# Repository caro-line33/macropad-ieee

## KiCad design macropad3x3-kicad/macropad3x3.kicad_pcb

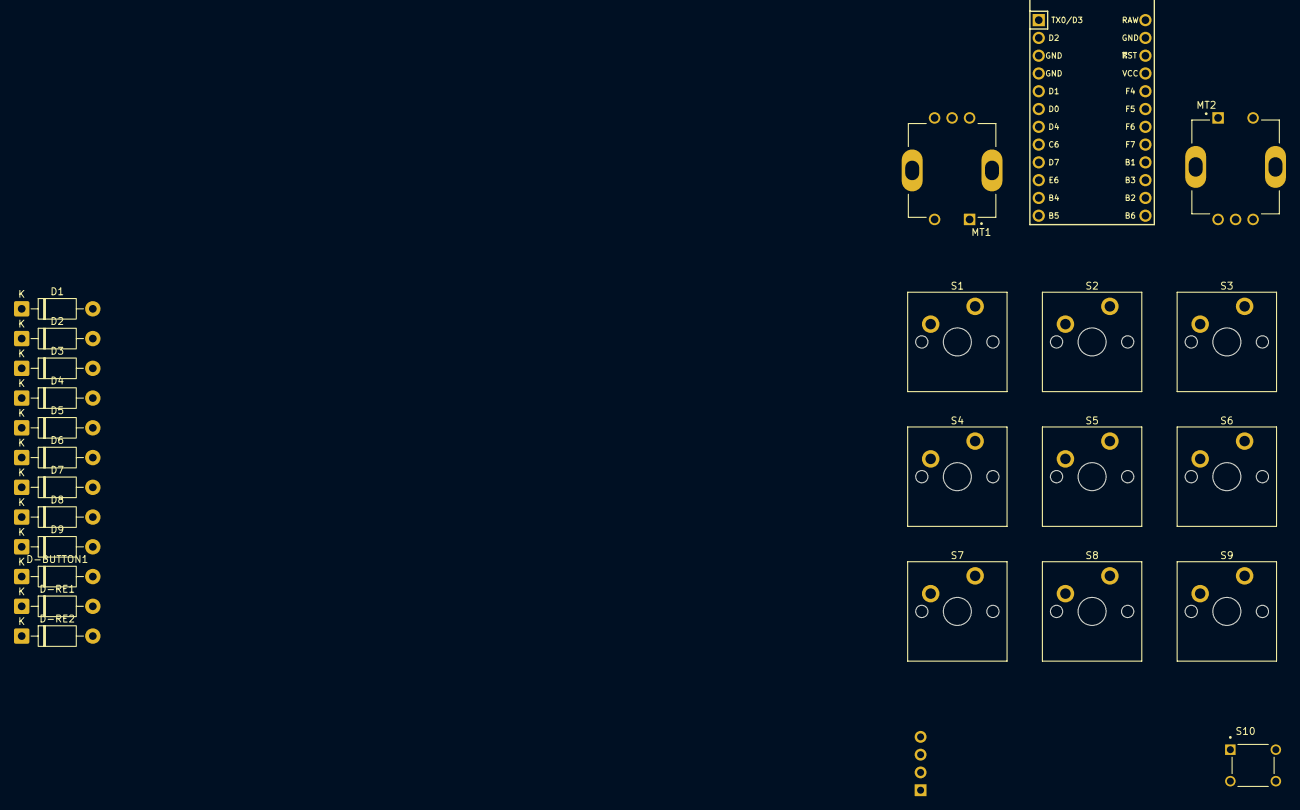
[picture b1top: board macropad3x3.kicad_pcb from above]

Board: 2 copper layers, 26 parts (0 on the bottom side), 20 nets, no tracks yet.

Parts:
D1, D2, D3, D4, D5, D6, D7, D8, D9: Diode; D_DO-41_SOD81_P10.16mm_Horizontal
D-BUTTON1: Diode; D_DO-41_SOD81_P10.16mm_Horizontal
D-RE1, D-RE2: Diode; D_DO-41_SOD81_P10.16mm_Horizontal
J1: OLED-4PIN; OLED_128x32
MT1, MT2: Rotary-Enc-Switch; XDCR_PEC11R-4215F-S0024
S1, S2, S3, S4, S5, S6, S7, S8, S9: Keyswitch; MX_PCB_1.00u
S10: TS02-66-95-BK-260-LCR-D; SW_TS02-66-95-BK-260-LCR-D
U1: Arduino_Pro_Micro

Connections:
/Button1: S2.1, S5.1, S8.1, S10.1
/Button2: D-BUTTON1.2 (A), S10.3
/RE1-1: MT1.1, S1.1, S4.1, S7.1
/RE1-2: D-RE1.2 (A), MT1.2
/RE2-1: MT2.1, S3.1, S6.1, S9.1
/RE2-2: D-RE2.2 (A), MT2.2
/row0: D-BUTTON1.1 (K), D-RE1.1 (K), D-RE2.1 (K)
/row1: D1.1 (K), D2.1 (K), D3.1 (K)
/row2: D4.1 (K), D5.1 (K), D6.1 (K)
/row3: D7.1 (K), D8.1 (K), D9.1 (K)
GND: MT1.COM, MT1.S1 (SHIELD), MT1.S2 (SHIELD), MT2.COM, MT2.S1 (SHIELD), MT2.S2 (SHIELD)
unnamed: D1.2 (A), S1.2
unnamed: D2.2 (A), S2.2
unnamed: D3.2 (A), S3.2
unnamed: D4.2 (A), S4.2
unnamed: D5.2 (A), S5.2
unnamed: D6.2 (A), S6.2
unnamed: D7.2 (A), S7.2
unnamed: D8.2 (A), S8.2
unnamed: D9.2 (A), S9.2

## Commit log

2025-09-06 created Kicad folder
2025-09-06 Added combined KiCAD symbols
2025-09-06 Added and linked footprints and 3d models
2025-09-06 schematic and pcb, matched outline to previous design
2025-09-09 added stuff
